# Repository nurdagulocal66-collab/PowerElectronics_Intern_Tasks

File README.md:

# PowerElectronics\_Intern\_Tasks

Staj Görevleri, LTspice Simülasyonları ve KiCad Donanım Tasarımları.

Bu proje, Fırçasız DC (BLDC) motorları sürebilmek için tasarlanmış bir güç katı  devresidir. Temelinde, klasik "H-Köprüsü" mantığının 3 fazlı motorlar için genişletilmiş hali olan 3'lü Yarım Köprü  topolojisi yer alır.

&#x20;Mikrodenetleyiciden gelen zayıf kontrol sinyalleri (PWM),  kapı sürücü (gate driver) entegreleri tarafından güçlendirilir. Bu PWM sinyalleri, devrenin anahtarlama elemanı olan 6 adet güç MOSFET'inin gatelerine iletilerek onların nano saniyeler içinde açılıp kapanmasını sağlar.

&#x20;6 MOSFET kesinlikle rastgele veya hepsi aynı anda açılmaz. Motoru döndürmek için 6 Adımlı Komütasyon denilen kusursuz bir sıra izlenir. Her adımda sadece 2 faz aktiftir: Bir fazın üst MOSFET'i  ve diğer bir fazın alt MOSFET'i açılır,3.faz boştadır. 

&#x20;Aynı faza ait alt ve üst MOSFET'ler, kısa devreyi önlemek için asla aynı anda açılmaz. Araya her zaman mikrosaniyelik bir ölü zaman (dead-time) konur.

&#x20;Bu ardışık aç-kapa işlemleri sonucunda ortaya çıkan bu yüksek akımlı enerji, kartın U, V ve W faz çıkışlarından motorun içindeki bobinlere iletilerek dönen bir manyetik alan yaratır ve rotoru döndürür.

&#x20;Motorun kararlı dönebilmesi için mikrodenetleyicinin, motorun içindeki mıknatısın (rotorun) o an fiziksel olarak nerede olduğunu bilmesi gerekir.

Hall sensörü olmayan motorlarda, rotorun konumunu bulmak için Back-EMF  yöntemi kullanılır. 6 adımlı komütasyon mantığında her an 2 faza akım verilirken, 3. faz her zaman boşta bırakılır.

&#x20;Motor dönerken tıpkı bir jeneratör gibi kendi içinde bir elektrik üretir. İşte boşta bırakılan bu 3. fazdan, motorun dönüşünden kaynaklanan Zıt EMK voltajı okunur. Bu sayede fiziksel bir sensöre ihtiyaç duymadan motorun anlık konumu tespit edilir ve bir sonraki PWM sinyalinin MOSFET'lere ne zaman gönderileceği kusursuz bir şekilde hesaplanır.

Bu proje, ilerleyen aşamalarda  motor sürücü kartı  olarak geliştirilebilir bir donanım altyapısına sahiptir. Tasarım sürecinde, sistemin kontrol edeceği motorun(42BLF01) maksimum tepe akımı 5.7 Amper olarak baz alınmıştır. Kart üzerindeki tüm yol genişlikleri, katman yerleşimleri ve komponent seçimleri tamamen bu akım değeri göz önüne alınarak yapılmıştır.

&#x20;Motorumuzun anlık olarak çekeceği 5.7A tepe akımının yolları eritmemesi, kartı aşırı ısıtmaması ve voltaj düşümüne  sebep olmaması için standart PCB kalınlık hesaplamalarını kullandık. 1 oz standart bakır kalınlığı için güç hatlarını ve motor faz çıkışlarını (U, V, W) 3 mm genişliğinde tasarlayarak kartın yüksek yük altında bile güvenle çalışmasını sağladık.Mikrodenetleyiciden çıkan, kapı sürücüye (gate driver) giden sinyal yollarını ve diğer lojik hatları 0.3 mm genişliğinde tuttuk.Bu yollardan yüksek bir akım geçmiyor, sadece veri ve tetikleme sinyalleri taşınıyor. Yolları ince tutarak hem kart üzerinde yer kazandık hem de sinyal yollarının birbirini etkilemesini engellemiş olduk.

&#x20; Kartın alt katmanını  hiç bölmeden tamamen kesintisiz bir toprak düzlemi  yaptık.

MOSFET'ler çok hızlı açılıp kapandığı için devrede ciddi bir elektromanyetik gürültü (EMI) oluşur. Alt katmandaki bu koca toprak alanı, gürültüyü emen bir kalkan görevi görerek kontrol sinyallerimizin temiz kalmasını sağlıyor.

&#x20;Motor anlık olarak 5.7A tepe akımı çekmek istediğinde özellikle ani kalkışlarda, güç hattında ciddi voltaj çökmeleri olur. 470 µF gibi büyük kapasiteli bu kapasitör, içinde yüksek miktarda enerji depolar. Hat gerilimi düşmeye çalıştığı anda bir pil gibi devreye girerek voltajı regüle eder ve sistemi besler. Güç girişine yakın konumlandırılmıştır.MOSFET'lerin nano saniyeler içinde açılıp kapanması, devrede  çok yüksek frekanslı elektriksel gürültüler (parazitler) üretir. 470 µF'lık büyük kapasitör hantaldır, bu hızlı gürültülere tepki veremez. İşte burada 100 nF devreye girer. Çok hızlı tepki veren bu minik kapasitörleri mosfet bacaklarının tam dibine koyduk. Böylece yüksek frekanslı parazitleri anında toprağa akıtarak devrenin güvenli çalışmasını sağladık.

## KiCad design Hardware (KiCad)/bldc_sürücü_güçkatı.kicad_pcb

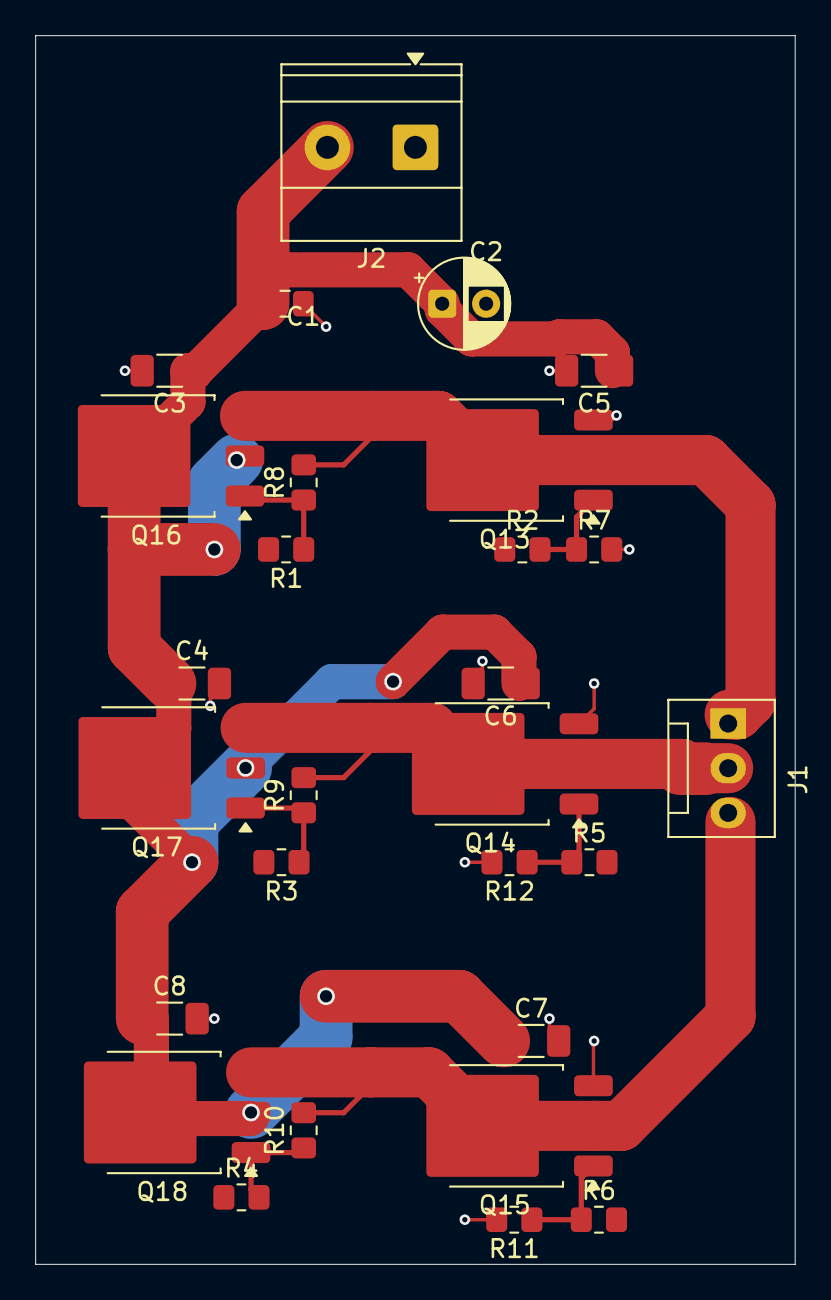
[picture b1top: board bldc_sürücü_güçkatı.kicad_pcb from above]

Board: 2 copper layers, 43.2 x 69.8 mm, 28 parts (0 on the bottom side), 11 nets.

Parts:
C1: 100nF; C_0805_2012Metric_Pad1.18x1.45mm_HandSolder
C2: 470uF; CP_Radial_D5.0mm_P2.50mm
C3, C4, C6, C7, C8: 100n; C_1206_3216Metric_Pad1.33x1.80mm_HandSolder
C5: 100nF; C_1206_3216Metric_Pad1.33x1.80mm_HandSolder
J1: Conn_01x03; FanPinHeader_1x03_P2.54mm_Vertical
J2: Screw_Terminal_01x02; TerminalBlock_Phoenix_MKDS-1,5-2_1x02_P5.00mm_Horizontal
Q13, Q14, Q15, Q16, Q17, Q18: IXTY64N055T; TO-252-3_TabPin2
R1, R2, R3, R4, R5, R6: 10; R_0805_2012Metric_Pad1.20x1.40mm_HandSolder
R7, R8, R9, R10, R11, R12: 4.7k; R_0805_2012Metric_Pad1.20x1.40mm_HandSolder

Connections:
+24V: C1.1, C2.1, C3.1, C4.1, C5.1, C6.1, C7.1, C8.1, J2.2, Q16.2 (D), Q17.2 (D), Q18.2 (D)
/MOTOR_A: J1.1, Q13.2 (D), Q16.3 (S), R8.2
/MOTOR_B: J1.2, Q14.2 (D), Q17.3 (S), R9.2
/MOTOR_C: J1.3, Q15.2 (D), Q18.3 (S), R10.2
GND: C1.2, C2.2, C3.2, C4.2, C5.2, C6.2, C7.2, C8.2, J2.1, Q13.3 (S), Q14.3 (S), Q15.3 (S), R7.2, R11.2, R12.2
unnamed: Q13.1 (G), R2.2, R7.1
unnamed: Q14.1 (G), R5.1, R12.1
unnamed: Q15.1 (G), R6.1, R11.1
unnamed: Q16.1 (G), R1.1, R8.1
unnamed: Q17.1 (G), R3.1, R9.1
unnamed: Q18.1 (G), R4.2, R10.1

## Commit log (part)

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2026-06-27 ilk commit
2026-06-28 Staj klasör yapısı ve README eklendi
